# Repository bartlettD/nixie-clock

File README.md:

# nixie-clock
A Nixie Tube based clock. Because everyone has to play with Nixies once, right?

## Introduction

The goal of this project is to design and contstruct a simple 4/6-Digit clock based around a set of [IN-12B Nixie Tubes](https://en.wikipedia.org/wiki/Nixie_tube). They are a type of cold-cathode display neon readout tube invented in the 1950's and used commonly in the USSR in volume manufacture until the 1980's after the rest of the world had moved on to 7-Segment LED arrays and other indicator technologies.

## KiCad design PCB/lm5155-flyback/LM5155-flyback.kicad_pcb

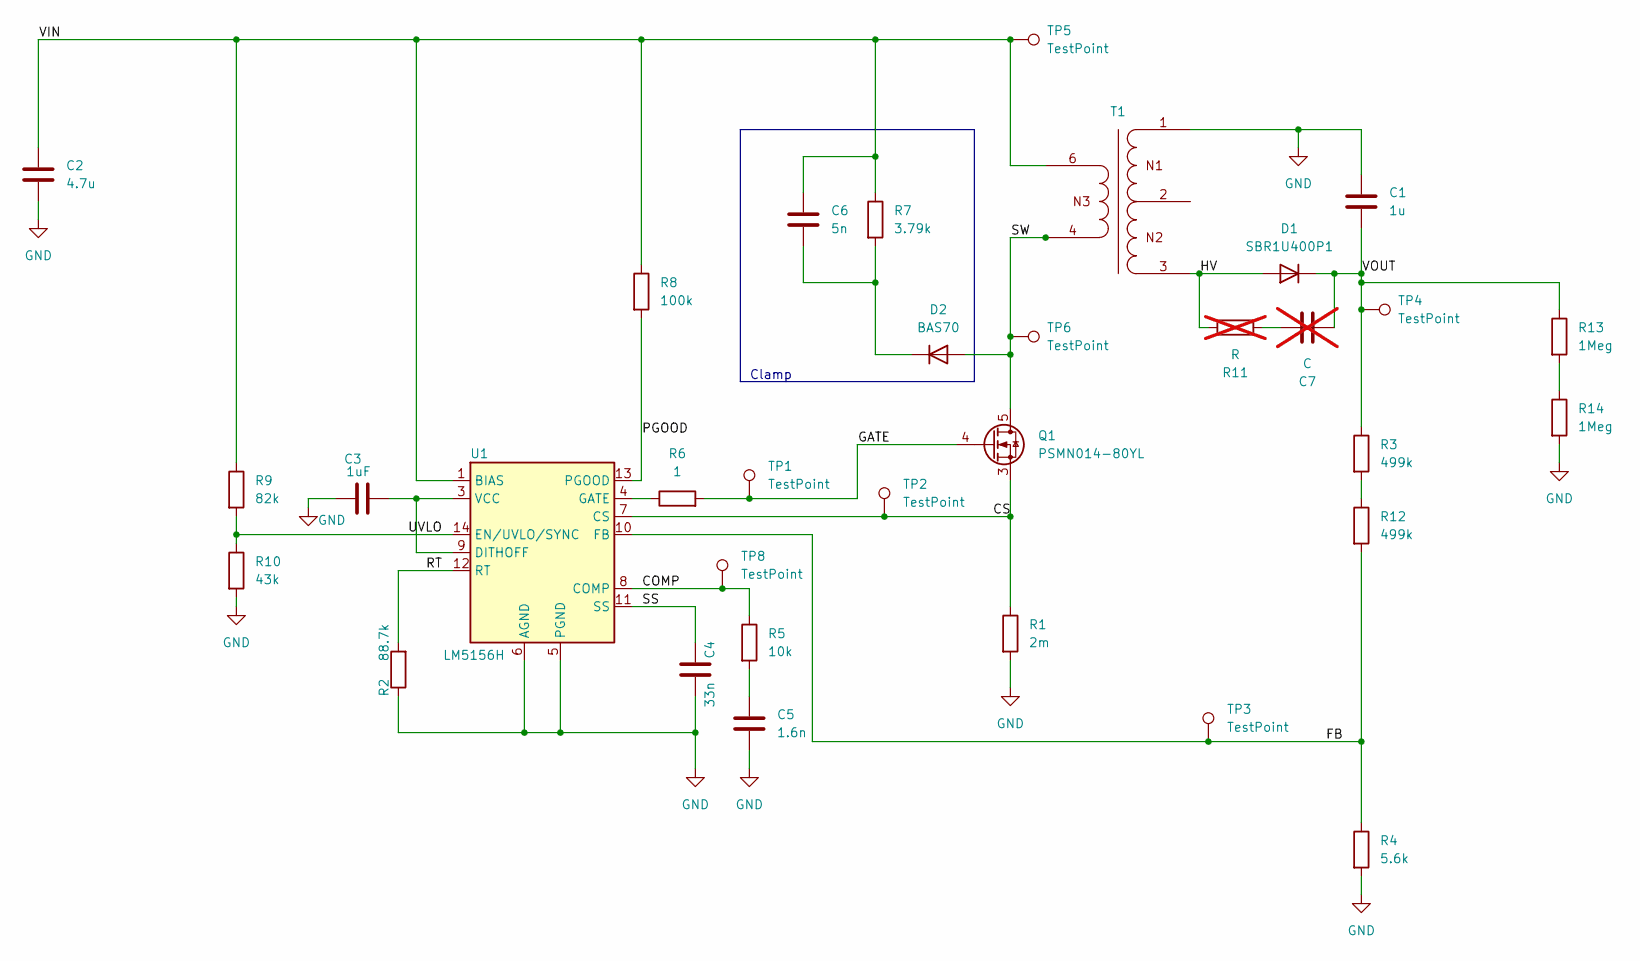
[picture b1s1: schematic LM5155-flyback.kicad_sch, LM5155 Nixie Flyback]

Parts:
C1: 1u; C_2220_5750Metric_Pad1.97x5.40mm_HandSolder
C2: 4.7u; C_0805_2012Metric_Pad1.18x1.45mm_HandSolder
C3: 1uF; C_0805_2012Metric_Pad1.18x1.45mm_HandSolder
C4: 33n; C_0805_2012Metric_Pad1.18x1.45mm_HandSolder
C5: 1.6n; C_0805_2012Metric_Pad1.18x1.45mm_HandSolder
C6: 5n; C_0805_2012Metric_Pad1.18x1.45mm_HandSolder
C7: C; C_0805_2012Metric_Pad1.18x1.45mm_HandSolder; not fitted
D1: SBR1U400P1; D_PowerDI-123
D2: BAS70; SOT-23
Q1: PSMN014-80YL; LFPAK56
R1: 2m; R_0805_2012Metric_Pad1.20x1.40mm_HandSolder
R2: 88.7k; R_0805_2012Metric_Pad1.20x1.40mm_HandSolder
R3, R12: 499k; R_0805_2012Metric_Pad1.20x1.40mm_HandSolder
R4: 5.6k; R_0805_2012Metric_Pad1.20x1.40mm_HandSolder
R5: 10k; R_0805_2012Metric_Pad1.20x1.40mm_HandSolder
R6: 1; R_0805_2012Metric_Pad1.20x1.40mm_HandSolder
R7: 3.79k; R_0805_2012Metric_Pad1.20x1.40mm_HandSolder
R8: 100k; R_0805_2012Metric_Pad1.20x1.40mm_HandSolder
R9: 82k; R_0805_2012Metric_Pad1.20x1.40mm_HandSolder
R10: 43k; R_0805_2012Metric_Pad1.20x1.40mm_HandSolder
R11: R; R_0805_2012Metric_Pad1.20x1.40mm_HandSolder; not fitted
R13, R14: 1Meg; R_0805_2012Metric_Pad1.20x1.40mm_HandSolder
T1: EP7-5801_750315825; T_Wurth_WE-FLYLT-EP7-5801; Part Number 750315825
TP1, TP2, TP3, TP4, TP5, TP6, TP8: TestPoint; TestPoint_Keystone_5019_Miniature
U1: LM5156H; Texas_HTSSOP-14-1EP_4.4x5mm_P0.65mm_EP3.4x5mm_Mask3.155x3.2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

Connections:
/COMP: R5.1, TP8.1 (1_1), U1.8 (COMP)
/CS: Q1.1 (S), Q1.2 (S), Q1.3 (S), R1.1, TP2.1 (1_1), U1.7 (CS)
/FB: R4.1, R12.2, TP3.1 (1_1), U1.10 (FB)
/GATE: Q1.4 (G), R6.2, TP1.1 (1_1)
/HV: D1.2 (A), R11.1, T1.3
/PGOOD: R8.2, U1.13 (PGOOD)
/RT: R2.2, U1.12 (RT)
/SS: C4.1, U1.11 (SS)
/SW: D2.1 (A), Q1.5 (D), T1.4, TP6.1 (1_1)
/UVLO: R9.2, R10.1, U1.14 (EN/UVLO/SYNC)
/VIN: C2.1, C6.1, R7.1, R8.1, R9.1, T1.6, TP5.1 (1_1), U1.1 (BIAS)
/VOUT: C1.2, C7.1, D1.1 (K), R3.1, R13.1, TP4.1 (1_1)
GND: C1.1, C2.2, C3.1, C4.2, C5.2, R1.2, R2.1, R4.2, R10.2, R14.2, T1.1, U1.5 (PGND), U1.6 (AGND), U1.15 (AGND)
unnamed: C5.1, R5.2
unnamed: C7.2, R11.2
unnamed: C6.2, D2.3 (K), R7.2
unnamed: R3.2, R12.1
unnamed: R13.2, R14.1
unnamed: C3.2, U1.3 (VCC), U1.9 (DITHOFF)
unnamed: R6.1, U1.4 (GATE)

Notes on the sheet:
Clamp

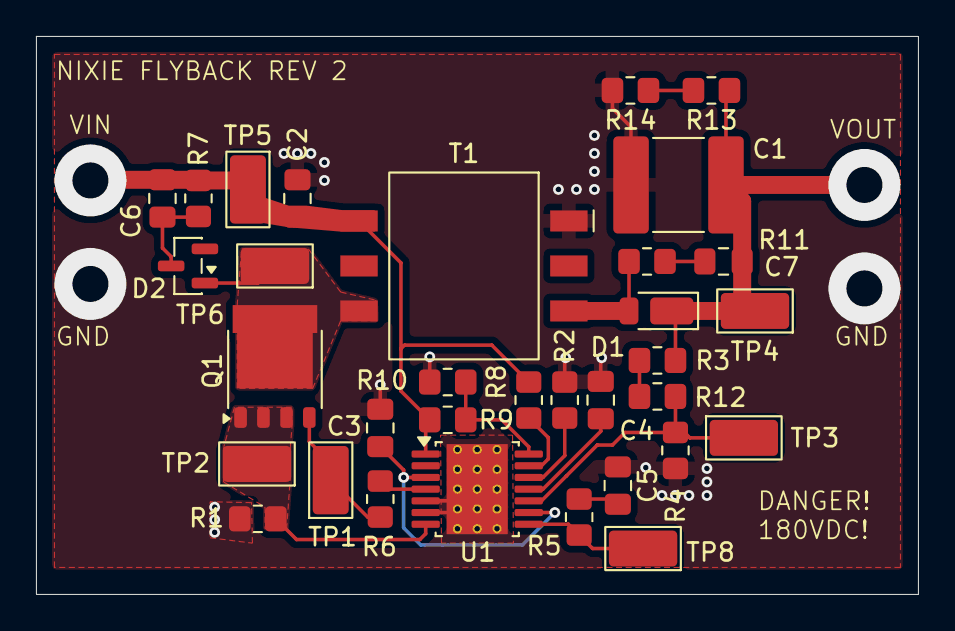
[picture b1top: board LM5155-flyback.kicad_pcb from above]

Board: 2 copper layers, 49.0 x 31.0 mm, 33 parts (0 on the bottom side), 20 nets.

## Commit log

2019-05-27 Adding Nixie Datasheet and AN-1126 appnote
2019-05-27 Adding rough simulation of a charge-pump multiplied Boost Circuit
2019-05-27 Starting on PCB, creating IN12-B footprint
2019-05-28 Add Charge Pump Doubler Simulation
2019-05-29 Improved charge pump circuit
2019-05-31 Adding simulation of LM3478 Boost converter in LTSPice and TINA-TI
2019-05-31 Add lm3478 datasheet
2019-06-03 Introduced Ideal FET and Diode for testing
2019-10-02 Adding spreadsheet to hold calculations for converter
2019-10-03 Fixed Symbol library path and Feedback Resistors
    Fixed the LM3478 symbol to point to a .lib within the current directory
    rather than in my own home directory. Makes cloning and running the sims
    on a new computer much easier.
    Fixed the parameter calculation for feedback resistors.
2019-10-03 Added some background to readme
2019-10-03 Doing some calcs for Boost Converter
2019-11-12 Playing with Jupyter Notebooks
2019-11-13 Working our more stuff
2019-11-14 Flyback stuff
2020-11-12 Work on some Boost Converter calculations
2020-11-13 Calculate inductance values vs frequency
2020-11-14 Further Boost Converter Calculations
2020-11-15 Develop calculation further. Replace ods with fods for better version tracking
2020-11-15 Start calculating RMS currents
2020-11-16 Fixing spreadsheet so LibreOffice V7 doesn't break it
2020-11-16 Fixing spreadsheet
2020-11-19 Calculate RMS currents for switch, diode, inductor.
2021-06-19 More spreadsheet work
2021-06-26 Just adding TODO to calc stuff
2021-07-11 Add simple diode loss calculation
2021-07-13 Inductor resistive losses and calculate total efficieny over inductance vs. frequency
2021-07-18 Extended calculated frequencies and created simple boost simulation
2021-07-24 Extended calculations
2021-07-24 Trying out sim in KiCad.
2021-07-25 Add sim for candidate Boost
2021-07-25 Move Models
2021-07-26 Advancing simulation
2021-07-30 Trying out boost concept
2021-08-08 Add charge pump to Nixie concept
2021-08-08 Calculations
2021-09-11 Start Flyback Idea
2026-01-13 Rework .gitignore so I can use pspice
2026-01-13 Small .gitignore tweak
2026-01-13 directory cleanup
2026-01-13 Add some stuff to .gitignore
2026-01-15 Flyback pspice simulations
2026-01-15 Updated flyback calculations, further flyback simulation
2026-01-16 Tidy up FET table
2026-01-17 Add another FET
2026-01-17 TPS40210 converter appears to be working. Still need to properly compensate the control loop
2026-01-27 Looking at an LM5155 based converter. Current-mode control is attractive
2026-01-28 More simulation. Import WIP LM5155 schematic
2026-02-02 Tweak gitignore
2026-02-02 Started flyback layout and tweak simulations
2026-02-02 More flyback layout. Almost done!
2026-02-03 Layout done. Send to fabricate
2026-02-03 Fix small issue with feedback resistors. Hopefully wont cause real issues with Rev 1
2026-05-11 Replaced LM5155 with LM5156H. Also replaced MOSFET. Packages just too difficult to solder.
2026-05-12 Layout changes
2026-05-12 upgrade project to kicad 10
2026-05-12 stop .history being added to repo
2026-06-04 Accidently used wrong figure for calculating secondary side conduction loss. Currently testing proper sense resistor sizing, completely messed that up!
